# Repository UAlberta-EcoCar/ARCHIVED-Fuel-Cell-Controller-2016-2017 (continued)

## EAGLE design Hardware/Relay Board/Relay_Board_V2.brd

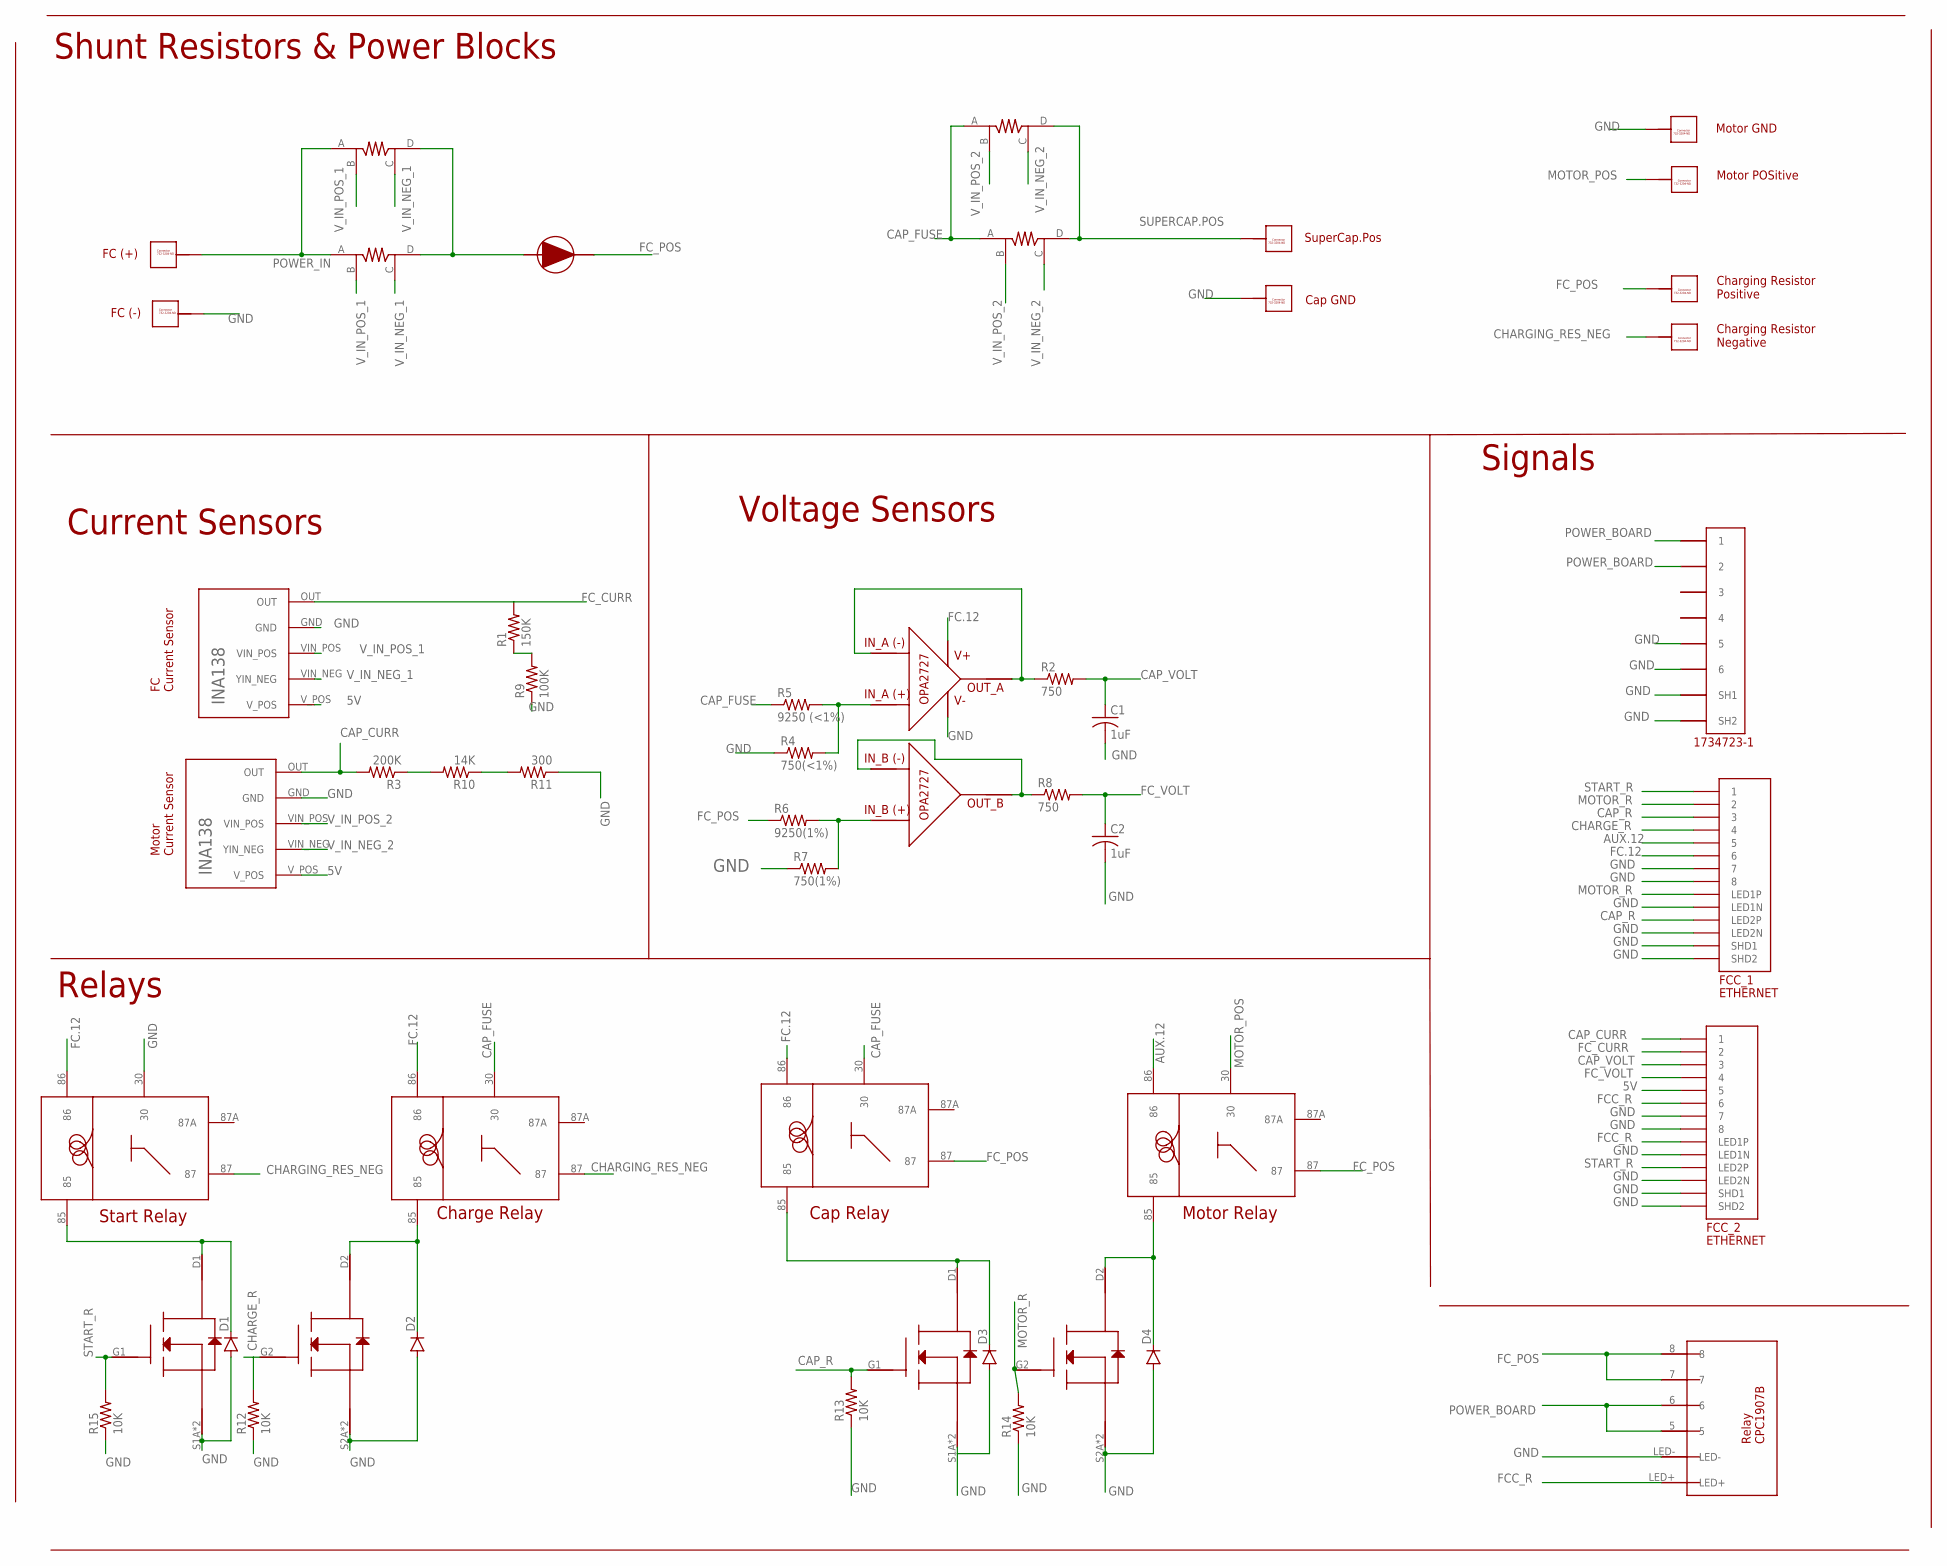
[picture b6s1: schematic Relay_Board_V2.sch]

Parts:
C1, C2: 1uF; C0805
CAP.GND, CAP.POS: 732-3204-ND_CONNECTOR; 732-3204-ND
CAP.RELAY: VCF4-1000
CAP.SHUNT.1, CAP.SHUNT.2: SHUNT_RESISTOR_CSM3637; CSM3637
CHARGE_RELAY: VCF4-1000
D1, D2, D3, D4: DIODESOD123; SOD-123
FC.CURR.SENSOR: TI_INA138
FC.GND, FC.POS: 732-3204-ND_CONNECTOR; 732-3204-ND
FC.SHUNT.1, FC.SHUNT.2: SHUNT_RESISTOR_CSM3637; CSM3637
FCC_1, FCC_2: ETHERNET; A122645-ND
FC_DIODE: DIODE-APT60S20BG
MOTOR.CURR.SENSOR: TI_INA138
MOTOR.GROUND, MOTOR.POSITIVE: 732-3204-ND_CONNECTOR; 732-3204-ND
MOTOR.RELAY: VCF4-1000
R1: 150K; R0805
R2, R8: 750; R0805
R3: 200K; R0805
R4: 750(<1%); R0805
R5: 9250 (<1%); R0805
R6: 9250(1%); R0805
R7: 750(1%); R0805
R9: 100K; R0805
R10: 14K; R0805
R11: 300; R0805
R12, R13, R14, R15: 10K; R0805
RES.NEG, RES.POS: 732-3204-ND_CONNECTOR; 732-3204-ND
START.RELAY: VCF4-1000
U$9, U$25: SI6926ADQ-T1-E3CT-ND_MOSFET
U$17: OP-AMP_OPA2727AIDR
U$19: 5555140-6; 1734723-1_RJ11
U$22: RELAY-CPC1907B

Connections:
5V: FC.CURR.SENSOR.V_POS, FCC_2.P$5 (5), MOTOR.CURR.SENSOR.V_POS
AUX.12: FCC_1.P$5 (5), MOTOR.RELAY.86
CAP_CURR: FCC_2.P$1 (1), MOTOR.CURR.SENSOR.OUT, R3.2
CAP_FUSE: CAP.RELAY.30, CAP.SHUNT.1.A, CAP.SHUNT.2.A, CHARGE_RELAY.30, R5.1
CAP_R: FCC_1.P$3 (3), FCC_1.P$12 (LED2P), R13.2, U$9.G1
CAP_VOLT: C1.1, FCC_2.P$3 (3), R2.2
CHARGE_R: FCC_1.P$4 (4), R12.2, U$25.G2
CHARGING_RES_NEG: CHARGE_RELAY.87, RES.NEG.P$1, RES.NEG.P$2, RES.NEG.P$3, RES.NEG.P$4, RES.NEG.P$5, RES.NEG.P$6, RES.NEG.P$7, RES.NEG.P$8, RES.NEG.P$9, RES.NEG.P$10, START.RELAY.87
FC.12: CAP.RELAY.86, CHARGE_RELAY.86, FCC_1.P$6 (6), START.RELAY.86, U$17.V+
FCC_R: FCC_2.P$6 (6), FCC_2.P$10 (LED1P), U$22.LED+
FC_CURR: FC.CURR.SENSOR.OUT, FCC_2.P$2 (2), R1.2
FC_POS: CAP.RELAY.87, FC_DIODE.CATHODE, MOTOR.RELAY.87, R6.1, RES.POS.P$1, RES.POS.P$2, RES.POS.P$3, RES.POS.P$4, RES.POS.P$5, RES.POS.P$6, RES.POS.P$7, RES.POS.P$8, RES.POS.P$9, RES.POS.P$10, U$22.7, U$22.8
FC_VOLT: C2.1, FCC_2.P$4 (4), R8.2
GND: C1.2, C2.2, CAP.GND.P$1, CAP.GND.P$2, CAP.GND.P$3, CAP.GND.P$4, CAP.GND.P$5, CAP.GND.P$6, CAP.GND.P$7, CAP.GND.P$8, CAP.GND.P$9, CAP.GND.P$10, D1.A, D2.A, D3.A, D4.A, FC.CURR.SENSOR.GND, FC.GND.P$1, FC.GND.P$2, FC.GND.P$3, FC.GND.P$4, FC.GND.P$5, FC.GND.P$6, FC.GND.P$7, FC.GND.P$8, FC.GND.P$9, FC.GND.P$10, FCC_1.P$7 (7), FCC_1.P$8 (8), FCC_1.P$9 (LED1N), FCC_1.P$11 (LED2N), FCC_1.P$13 (SHD1), FCC_1.P$14 (SHD2), FCC_2.P$7 (7), FCC_2.P$8 (8), FCC_2.P$9 (LED1N), FCC_2.P$11 (LED2N), FCC_2.P$13 (SHD1), FCC_2.P$14 (SHD2), MOTOR.CURR.SENSOR.GND, MOTOR.GROUND.P$1, MOTOR.GROUND.P$2, MOTOR.GROUND.P$3, MOTOR.GROUND.P$4, MOTOR.GROUND.P$5, MOTOR.GROUND.P$6, MOTOR.GROUND.P$7, MOTOR.GROUND.P$8, MOTOR.GROUND.P$9, MOTOR.GROUND.P$10, R4.1, R7.1, R9.1, R11.1, R12.1, R13.1, R14.1, R15.1, START.RELAY.30, U$9.S1A (S1), U$9.S1B (S1), U$9.S2A (S2), U$9.S2B (S2), U$17.V-, U$19.5, U$19.6, U$19.SH1, U$19.SH2, U$22.LED-, U$25.S1A (S1), U$25.S1B (S1), U$25.S2A (S2), U$25.S2B (S2)
MOTOR_POS: MOTOR.POSITIVE.P$1, MOTOR.POSITIVE.P$2, MOTOR.POSITIVE.P$3, MOTOR.POSITIVE.P$4, MOTOR.POSITIVE.P$5, MOTOR.POSITIVE.P$6, MOTOR.POSITIVE.P$7, MOTOR.POSITIVE.P$8, MOTOR.POSITIVE.P$9, MOTOR.POSITIVE.P$10, MOTOR.RELAY.30
MOTOR_R: FCC_1.P$2 (2), FCC_1.P$10 (LED1P), R14.2, U$9.G2
unnamed: R1.1, R9.2
unnamed: CAP.RELAY.85, D3.C, U$9.D1
unnamed: D1.C, START.RELAY.85, U$25.D1
unnamed: CHARGE_RELAY.85, D2.C, U$25.D2
unnamed: R4.2, R5.2, U$17.IN_A+
unnamed: R6.2, R7.2, U$17.IN_B+
unnamed: R8.1, U$17.IN_B-, U$17.OUT_B
unnamed: R2.1, U$17.IN_A-, U$17.OUT_A
unnamed: R3.1, R10.2
unnamed: R10.1, R11.2
unnamed: D4.C, MOTOR.RELAY.85, U$9.D2
POWER_BOARD: U$19.1, U$19.2, U$22.5, U$22.6
POWER_IN: FC.POS.P$1, FC.POS.P$2, FC.POS.P$3, FC.POS.P$4, FC.POS.P$5, FC.POS.P$6, FC.POS.P$7, FC.POS.P$8, FC.POS.P$9, FC.POS.P$10, FC.SHUNT.1.A, FC.SHUNT.2.A
SHUNT_RES_1: FC.SHUNT.1.D, FC.SHUNT.2.D, FC_DIODE.ANODE
START_R: FCC_1.P$1 (1), FCC_2.P$12 (LED2P), R15.2, U$25.G1
SUPERCAP.POS: CAP.POS.P$1, CAP.POS.P$2, CAP.POS.P$3, CAP.POS.P$4, CAP.POS.P$5, CAP.POS.P$6, CAP.POS.P$7, CAP.POS.P$8, CAP.POS.P$9, CAP.POS.P$10, CAP.SHUNT.1.D, CAP.SHUNT.2.D
V_IN_NEG_1: FC.CURR.SENSOR.VIN_NEG (YIN_NEG), FC.SHUNT.1.C, FC.SHUNT.2.C
V_IN_NEG_2: CAP.SHUNT.1.C, CAP.SHUNT.2.C, MOTOR.CURR.SENSOR.VIN_NEG (YIN_NEG)
V_IN_POS_1: FC.CURR.SENSOR.VIN_POS, FC.SHUNT.1.B, FC.SHUNT.2.B
V_IN_POS_2: CAP.SHUNT.1.B, CAP.SHUNT.2.B, MOTOR.CURR.SENSOR.VIN_POS

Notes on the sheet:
FC Current Sensor
SuperCap.Pos
Charging Resistor Positive
Charging Resistor Negative
Motor Current Sensor
FC (+)
FC (-)
Motor POSitive
Voltage Sensors
Current Sensors
Relays
Cap Relay
Charge Relay
Start Relay
Motor Relay
Motor GND
Cap GND
Shunt Resistors & Power Blocks
Signals

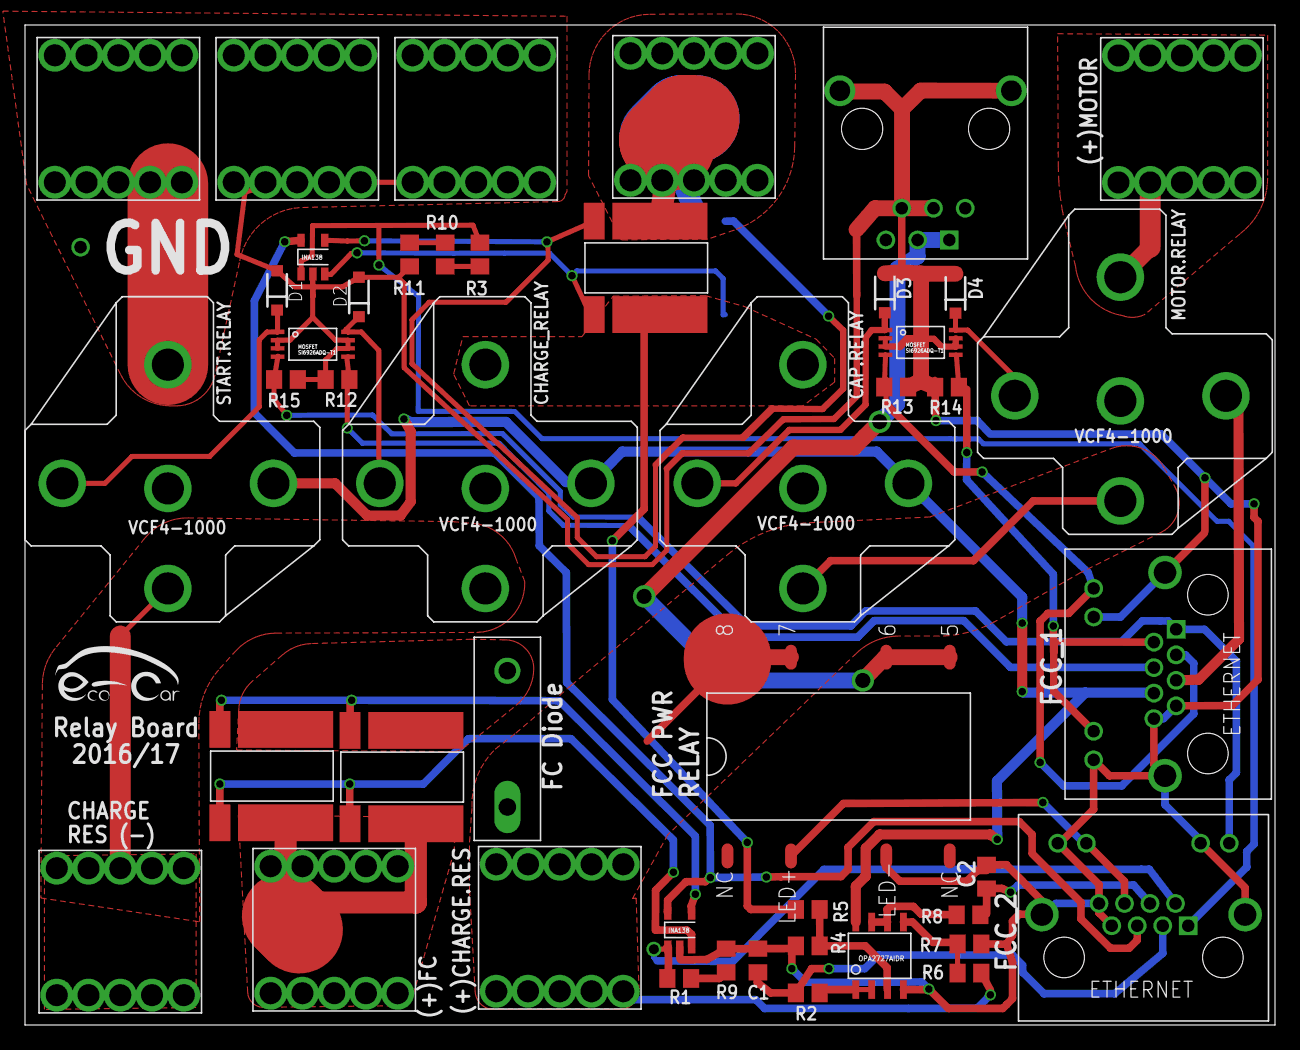
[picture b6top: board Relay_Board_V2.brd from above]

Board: 2 copper layers, 100.0 x 80.0 mm, 48 parts (1 on the bottom side), 36 nets.

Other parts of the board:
U$16: LOGO

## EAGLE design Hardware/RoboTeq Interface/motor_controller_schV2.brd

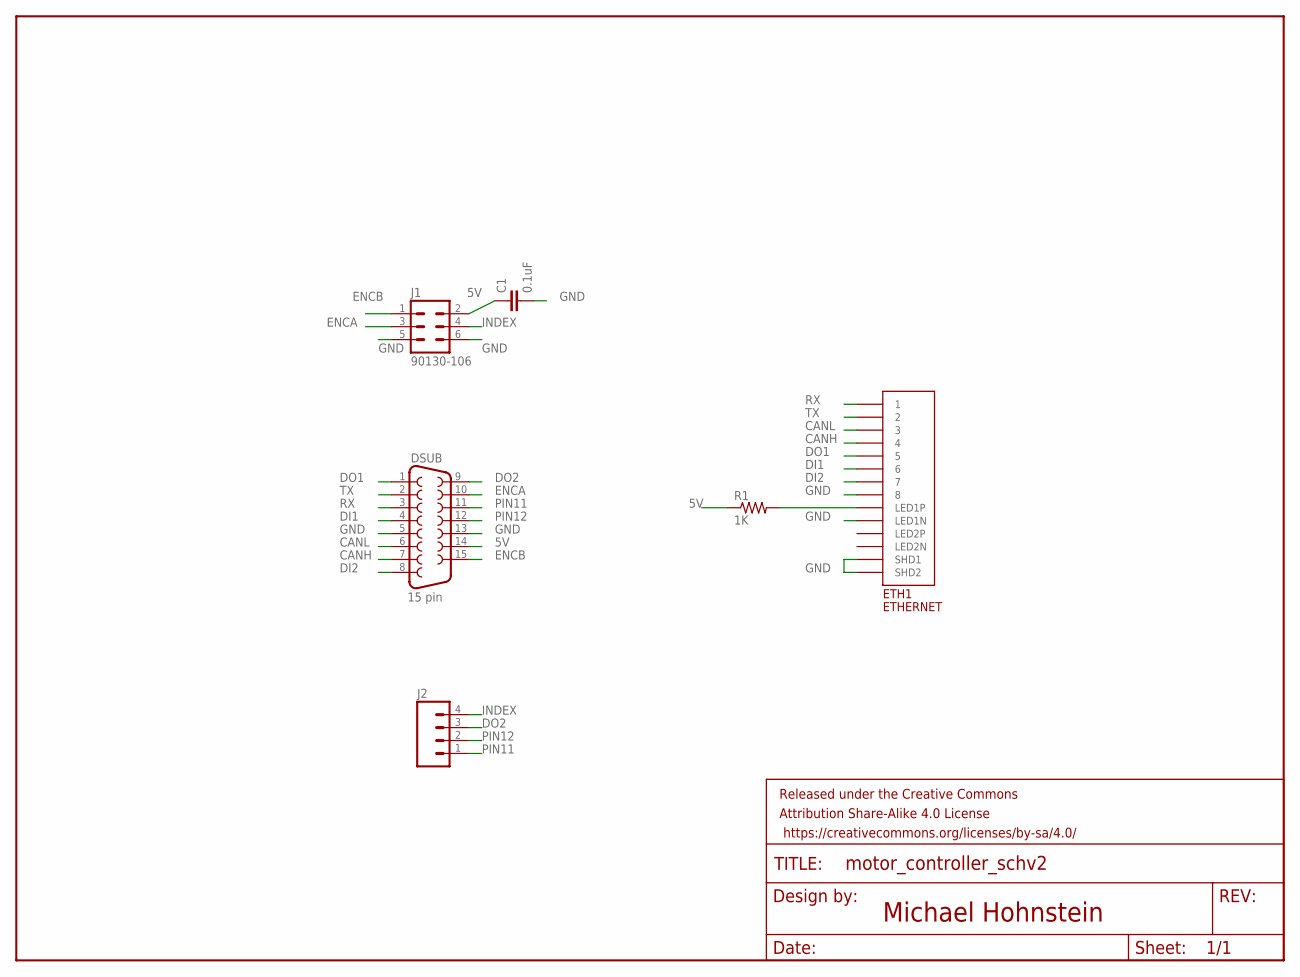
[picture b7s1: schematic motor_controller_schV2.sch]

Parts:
C1: 0.1uF; 0603-CAP
DSUB: 15 pin; F15HP
ETH1: ETHERNET; A122645-ND
FRAME1: FRAME-LETTER; CREATIVE_COMMONS
J1: 90130-106; 90130-1?06
J2: M04PTH; 1X04
R1: 1K; 0603-RES

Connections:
5V: C1.1, DSUB.14, J1.2, R1.1
CANH: DSUB.7, ETH1.P$4 (4)
CANL: DSUB.6, ETH1.P$3 (3)
DI1: DSUB.4, ETH1.P$6 (6)
DI2: DSUB.8, ETH1.P$7 (7)
DO1: DSUB.1, ETH1.P$5 (5)
DO2: DSUB.9, J2.3
ENCA: DSUB.10, J1.3
ENCB: DSUB.15, J1.1
GND: C1.2, DSUB.5, DSUB.13, ETH1.P$8 (8), ETH1.P$9 (LED1N), ETH1.P$13 (SHD1), ETH1.P$14 (SHD2), J1.5, J1.6
INDEX: J1.4, J2.4
unnamed: ETH1.P$10 (LED1P), R1.2
PIN11: DSUB.11, J2.1
PIN12: DSUB.12, J2.2
RX: DSUB.3, ETH1.P$1 (1)
TX: DSUB.2, ETH1.P$2 (2)

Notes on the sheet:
Michael Hohnstein

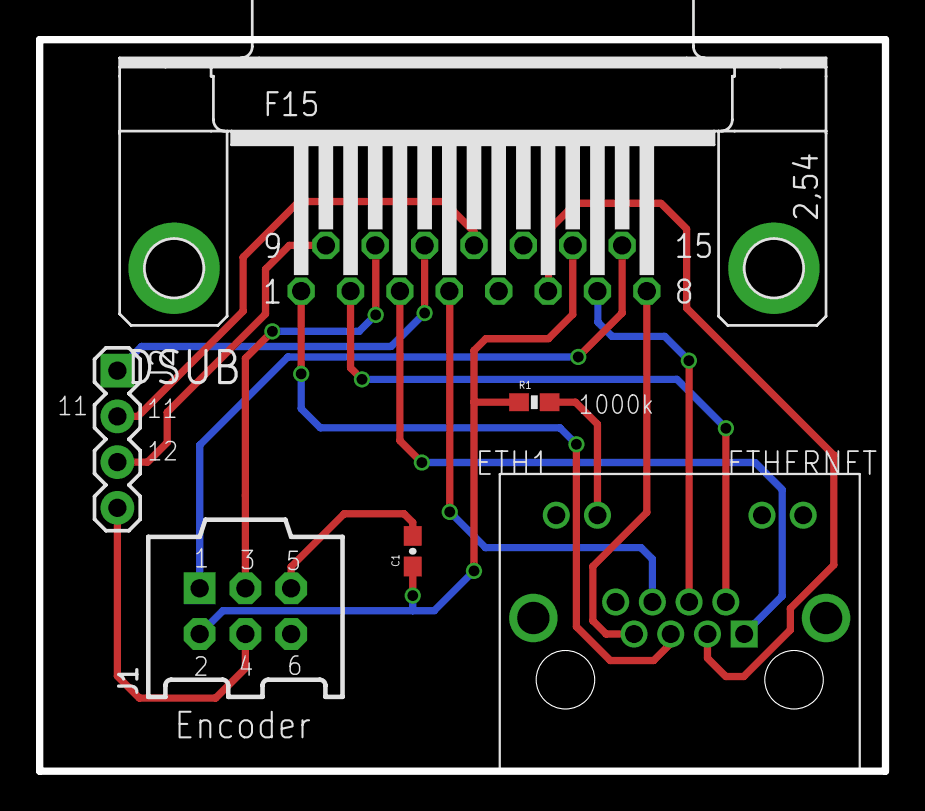
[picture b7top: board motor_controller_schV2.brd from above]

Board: 2 copper layers, 47.0 x 40.6 mm, 7 parts (0 on the bottom side), 16 nets.

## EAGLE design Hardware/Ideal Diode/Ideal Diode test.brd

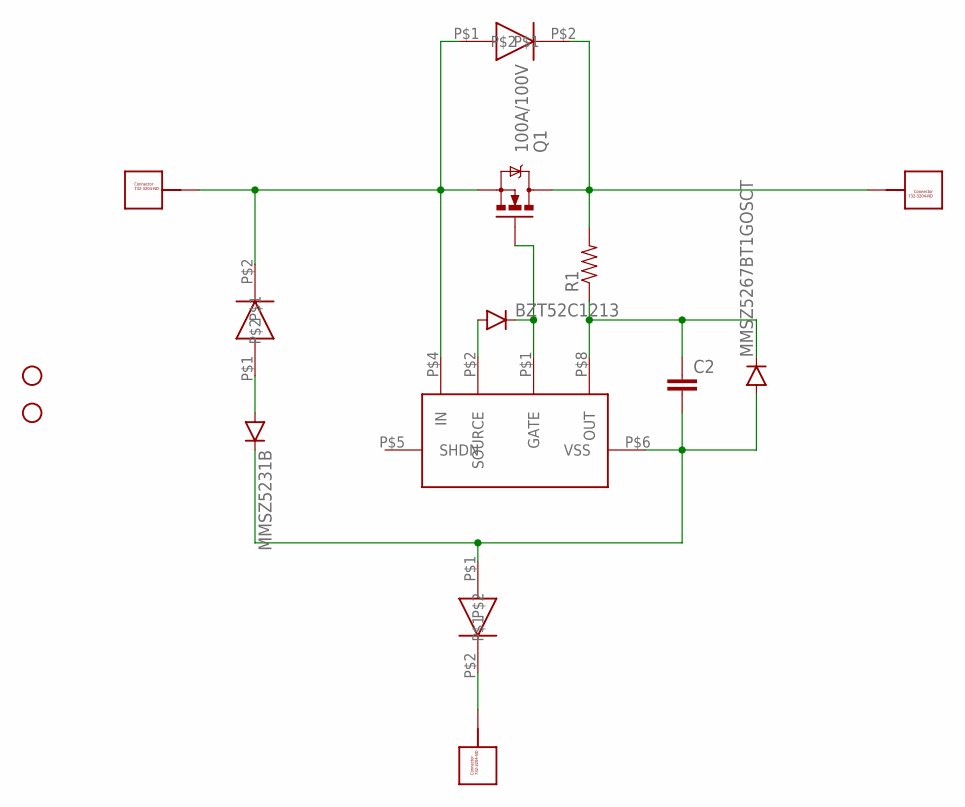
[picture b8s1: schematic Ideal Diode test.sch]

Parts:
BZT52C1213: DIODESOD123; SOD-123
C2: CAP0603-CAP; 0603-CAP
MMSZ5231B, MMSZ5267BT1GOSCT: DIODESOD123; SOD-123
Q1: 100A/100V; TO-263/D2PAK
R1: RESISTOR0603-RES; 0603-RES
S1B: DIODE; SMA
SMAJ70A, SMAJ150A: DIODE; SMA
STANDOFF1, STANDOFF2: STAND-OFF
U$1: LTC359; LTC4359
U$2, U$3, U$4: 732-3204-ND_CONNECTOR; 732-3204-ND

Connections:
GND: S1B.P$2, U$4.P$1, U$4.P$2, U$4.P$3, U$4.P$4, U$4.P$5, U$4.P$6, U$4.P$7, U$4.P$8, U$4.P$9, U$4.P$10
unnamed: Q1.3 (S), SMAJ70A.P$2, SMAJ150A.P$1, U$1.P$4 (IN), U$3.P$1, U$3.P$2, U$3.P$3, U$3.P$4, U$3.P$5, U$3.P$6, U$3.P$7, U$3.P$8, U$3.P$9, U$3.P$10
unnamed: Q1.2 (D), R1.2, SMAJ150A.P$2, U$2.P$1, U$2.P$2, U$2.P$3, U$2.P$4, U$2.P$5, U$2.P$6, U$2.P$7, U$2.P$8, U$2.P$9, U$2.P$10
unnamed: C2.1, MMSZ5267BT1GOSCT.C, R1.1, U$1.P$8 (OUT)
unnamed: BZT52C1213.A, U$1.P$2 (SOURCE)
unnamed: BZT52C1213.C, Q1.1 (G), U$1.P$1 (GATE)
unnamed: C2.2, MMSZ5231B.C, MMSZ5267BT1GOSCT.A, S1B.P$1, U$1.P$6 (VSS)
unnamed: MMSZ5231B.A, SMAJ70A.P$1

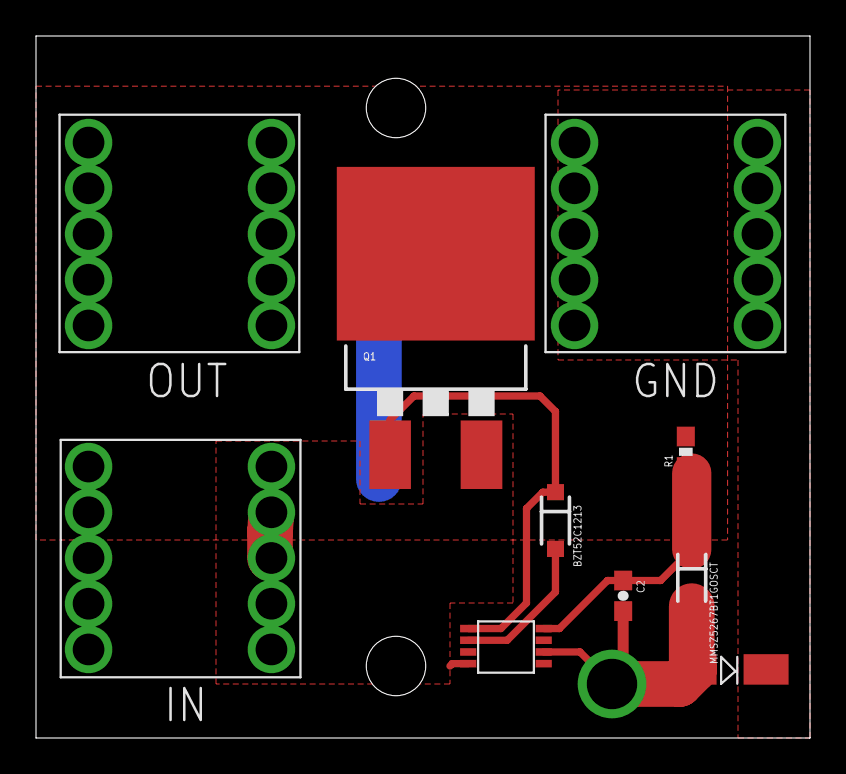
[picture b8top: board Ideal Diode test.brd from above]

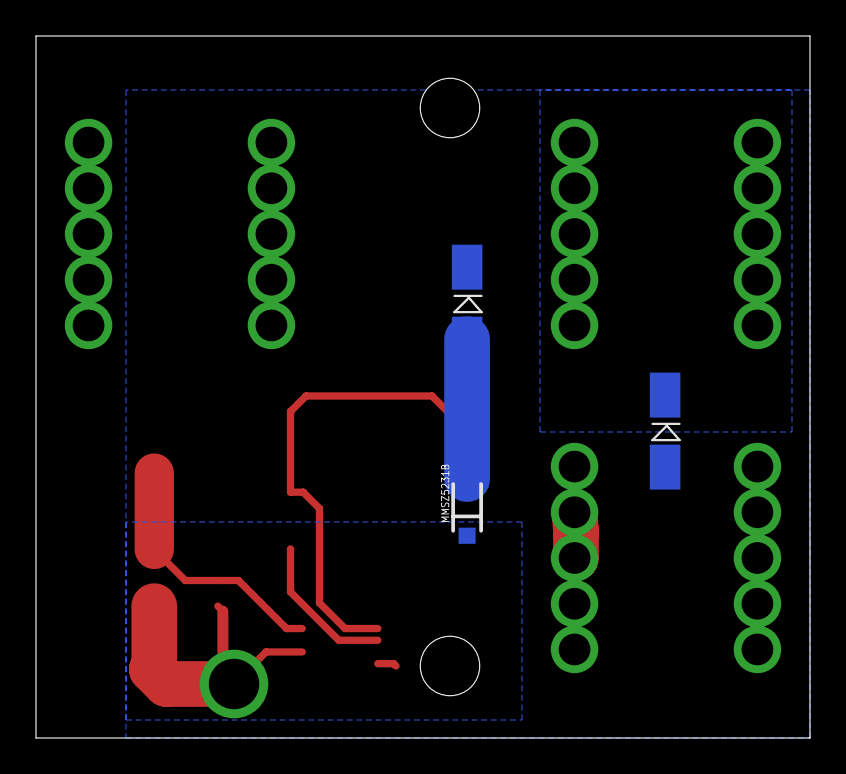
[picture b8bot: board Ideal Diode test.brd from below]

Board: 2 copper layers, 43.0 x 39.0 mm, 15 parts (3 on the bottom side), 8 nets.

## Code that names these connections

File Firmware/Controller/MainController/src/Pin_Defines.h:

#ifndef PIN_DEFINES_H
#define PIN_DEFINES_H

#include "mbed.h"

//LED
#define STATUS_LED PB_14

//Valves
#define SUPPLY_V PA_5
#define PURGE_V PA_6
#define EXTRA_V PA_7

//relays
#define CAP_R PD_14
#define CHARGE_R PD_15
#define FCC_R PF_12
#define START_R PF_13
#define MOTOR_R PE_9

//analog voltage readings
#define CAPVOLT PC_0
#define FCCURR PC_3
#define FCVOLT PF_3
#define CAPCURR PF_5
#define FCPRES PF_10

//Multiplexor pins
#define MULTO2 PF_15
#define MULTA PE_13
#define MULTB PF_14
#define MULTO1 PE_11

//Serial
//data link
#define LINK_RX PE_7//Rx7
#define LINK_TX PE_8//Tx7
//open log
#define OL_RX PB_11//Rx3
#define OL_TX PB_10//Tx3

//I2C
#define I2C_SDA PD_13 //I2C4_SDA
#define I2C_SCL PD_12 //I2C4_SCL

#endif

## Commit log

2016-11-08 pinout list
2016-11-10 mosfet board schematic done
2016-11-14 updated fan controller
2016-12-20 added power board
2016-12-20 added rs 232 converter
2016-12-21 fcc schematic mostly done
2016-12-21 added connector for motor
2016-12-27 added lots of pull down/up resistors and leds
2016-12-27 main board routed
2016-12-28 added ground vias, making silk screen nice, starting documentation
2017-01-04 updated caps on fcc rs232 driver
2017-01-04 undo delete cvm board
2017-01-06 updated relay board
2017-01-06 added gerbers
2017-01-09 couple board revisions
2017-01-09 cleaned up silk screens
2017-01-11 boards that will be ordered
2017-01-11 created v2 s of everything
2017-01-14 part list for CVM board
2017-01-28 added some example code and libraries
2017-01-28 more libraries, not sure if they will work
2017-01-28 some pin definitions
2017-01-28 slowly putting together functions for mbed rtos
2017-01-28 code is working :)
2017-01-28 Added mikes board
2017-01-28 Power Board
2017-01-28 added a start up squence thread
2017-01-29 can read temp/humidity sensor
2017-01-29 turn sht31 functions into a thread
2017-01-29 bunch of i2c stuff done
2017-02-18 another update
2017-02-18 I changed some stuff
    details are here
2017-02-19 got bluetooth working
2017-02-21 undid accidental changes to CVM code
2017-02-23 Small Changes
2017-02-24 Current CVM code, compiles, liz's changes(made before I understood how to use git, now I do-ish)
2017-02-26 temp sensor, rtc, and status leds working on new controller
2017-02-26 more data logging
2017-02-28 shut down and error checking added
2017-03-04 edited cvm code
2017-03-08 Changed Delay time and moved test files
    Changed delay time
    switched from classic delay to while (millis()... for greater
    accuracy.
    Moved test files
    Created a new file for the test code.
2017-03-19 updated fc power board
2017-03-19 fc power board update
2017-03-20 cleaned up fc power board silk screen
2017-03-20 power board gerbers
2017-03-20 The test files for testing one I2C chip
2017-03-20 trying to get git to work
2017-03-20 old code new code in the CVM folder
2017-03-20 old files new files in CVM folder
2017-03-20 CVM code with working serial print and signal 1 and 2 functions
2017-03-20 moving files
2017-03-21 Working CVM code for one channel on one chip
2017-03-25 cleaning up the code
2017-03-26 voltage divider calculations for CVM Board
2017-04-01 Attempted to Calibrate Voltage Readings
2017-04-04 working test code, shows values of each channel based on colour of the wire for ease of testing
2017-04-04 almost done just need to fix voltage adjustment
2017-04-05 more polished cvm code and test code both in theory finshed
2017-04-10 calibrated fc current sensor and programed in some safe guards to prevent me from doing stupid things
2017-04-13 edits to adjust for broken channels on adc's
2017-04-16 Yay controller apears to be working!!!!!!
2017-04-17 working code, accurate voltage readings
2017-04-21 more testing completed
2017-04-22 prototype works
2017-04-29 commit before switching to alice
2017-04-30 Fc seems to run after it self destructed
2017-05-09 commiting changes made during comp
2017-05-19 new independent mosfet board
2017-09-24 Updated pins from teensy to Nucleo. May need to be changed based on how the board is layed out. Updated platform.ino to Nucleo.
2017-10-07 got rid of redundant ground traces
2017-10-07 removed more useless ground traces. Moved caps for xtal closer to the actual crystal
2017-10-07 more general clean up. Moved LEDs to top layer. Removed some useless traces. Fixed warnings
2017-10-08 added 3.3V LDO (chip and all digital signals are all 3.3V now). Added appropriate voltage divider for hydrogen sensor output (with optional cap)
2018-02-10 FC power board updated
    updated board gerbers generated
2018-02-11 Added folder with main controller code adjusted for Alice
